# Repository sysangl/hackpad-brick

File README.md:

> This was a hackpad built for Hackclub's YSWS. Check them out [here](https://hackclub.com/)!

## Overview
I'm lazy, so what better thing to do than spend hours learning how to and trying to design a PCB and case for a macro pad, just so I can save milliseconds pressing one key instead of two.s

After days of wondering which way diodes should face in a keyboard matrix, I present the macroPAD (such original naming, i know).

## TODO
- I will finish/refine the KMK code when I have the PCB
- Design an angled stand.
- Rotary Encoder Knob.

## Features
- Outfitted with enough keys to play games such as Minecraft
- Quick-switch keybind profiles, in case you're like me and keep switching between something productive and something not
- Nice little OLED screen for all the customisation you would never need
- And, an integrated stand built into the case (if I remembered to add it)

## SCHEMATIC
![[PCB Schematic]](./assets/SCHEM.png)

## PCB
![[PCB]](./assets/PCB.png)

## CASE
The case went through 4 major redesigns, and will probably change again in the future.
![[Case Design in Fusion]](./assets/CaseV3.png)
![[Case Design in Fusion]](./assets/CaseV3-Main.png)

## BOM:
What you need:
- 11x Cherry MX Switches
- 11x DSA Keycaps
- 5x M3x5x4 Heatset inserts
- 4x M3x16mm SHCS Bolts
- 1x M3x12mm SHCS Bolts
- 12x 1N4148 DO-35 Diodes.
- 1x 0.91" 128x32 OLED Display
- 1x EC11 Rotary Encoder
- 1x XIAO RP2040
- 1x 3D Printed Case (Top Cover & Main Case - Black, Middle Plate - White)

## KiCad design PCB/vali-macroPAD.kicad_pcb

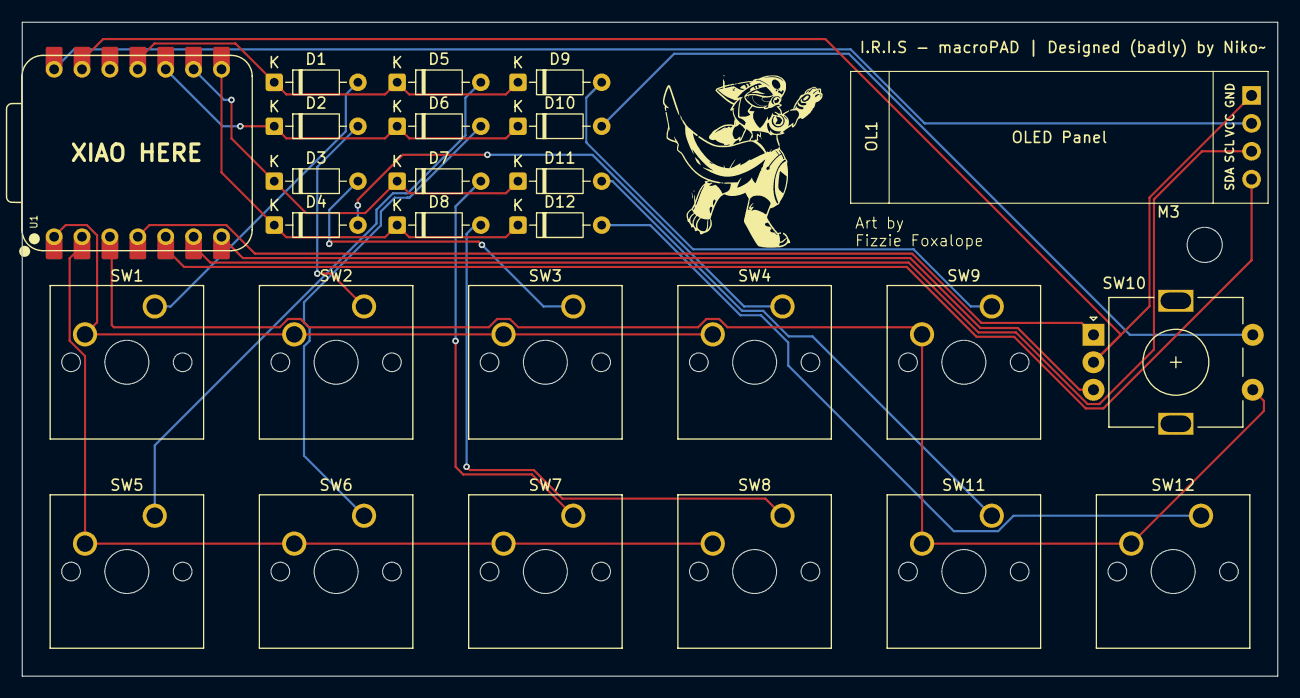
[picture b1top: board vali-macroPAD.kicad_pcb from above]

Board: 2 copper layers, 114.3 x 59.5 mm, 27 parts (0 on the bottom side), 25 nets.

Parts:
D1, D2, D3, D4, D5, D6, D7, D8, D9, D10, D11, D12: 1N4148; D_DO-35_SOD27_P7.62mm_Horizontal
M3: MountingHole_3.2mm_M3
OL1: OLED; SSD1306-0.91-OLED-4pin-128x32
SW1, SW2, SW3, SW4, SW5, SW6, SW7, SW8, SW9, SW11, SW12: SW_Push; SW_Cherry_MX_1.00u_PCB
SW10: RotaryEncoder_Switch; RotaryEncoder_Alps_EC11E-Switch_Vertical_H20mm
U1: XIAO-RP2040-DIP

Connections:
Col1: D1.1 (K), D5.1 (K), D9.1 (K), U1.11 (GPIO3/MOSI)
Col2: D2.1 (K), D6.1 (K), D10.1 (K), U1.10 (GPIO4/MISO)
Col3: D3.1 (K), D7.1 (K), D11.1 (K), U1.9 (GPIO2/SCK)
Col4: D4.1 (K), D8.1 (K), D12.1 (K), U1.8 (GPIO1/RX)
GND: OL1.1 (SDA), SW10.C, U1.13 (GND)
unnamed: D1.2 (A), SW1.1
unnamed: D2.2 (A), SW2.1
unnamed: D3.2 (A), SW3.1
unnamed: D4.2 (A), SW4.1
unnamed: D5.2 (A), SW5.1
unnamed: D6.2 (A), SW6.1
unnamed: D7.2 (A), SW7.1
unnamed: D8.2 (A), SW8.1
unnamed: D9.2 (A), SW9.1
unnamed: D10.2 (A), SW10.S2
unnamed: D11.2 (A), SW11.1
unnamed: D12.2 (A), SW12.1
OLEDSCL: OL1.3 (VCC), U1.6 (GPIO7/SCL)
OLEDSDA: OL1.4 (GND), U1.5 (GPIO6/SDA)
REA: SW10.A, U1.4 (GPIO29/ADC3/A3)
REB: SW10.B, U1.7 (GPIO0/TX)
Row1: SW1.2, SW2.2, SW3.2, SW4.2, U1.1 (GPIO26/ADC0/A0)
Row2: SW5.2, SW6.2, SW7.2, SW8.2, U1.2 (GPIO27/ADC1/A1)
Row3: SW9.2, SW10.S1, SW11.2, SW12.2, U1.3 (GPIO28/ADC2/A2)
VCC: OL1.2 (SCL), U1.14 (VBUS)

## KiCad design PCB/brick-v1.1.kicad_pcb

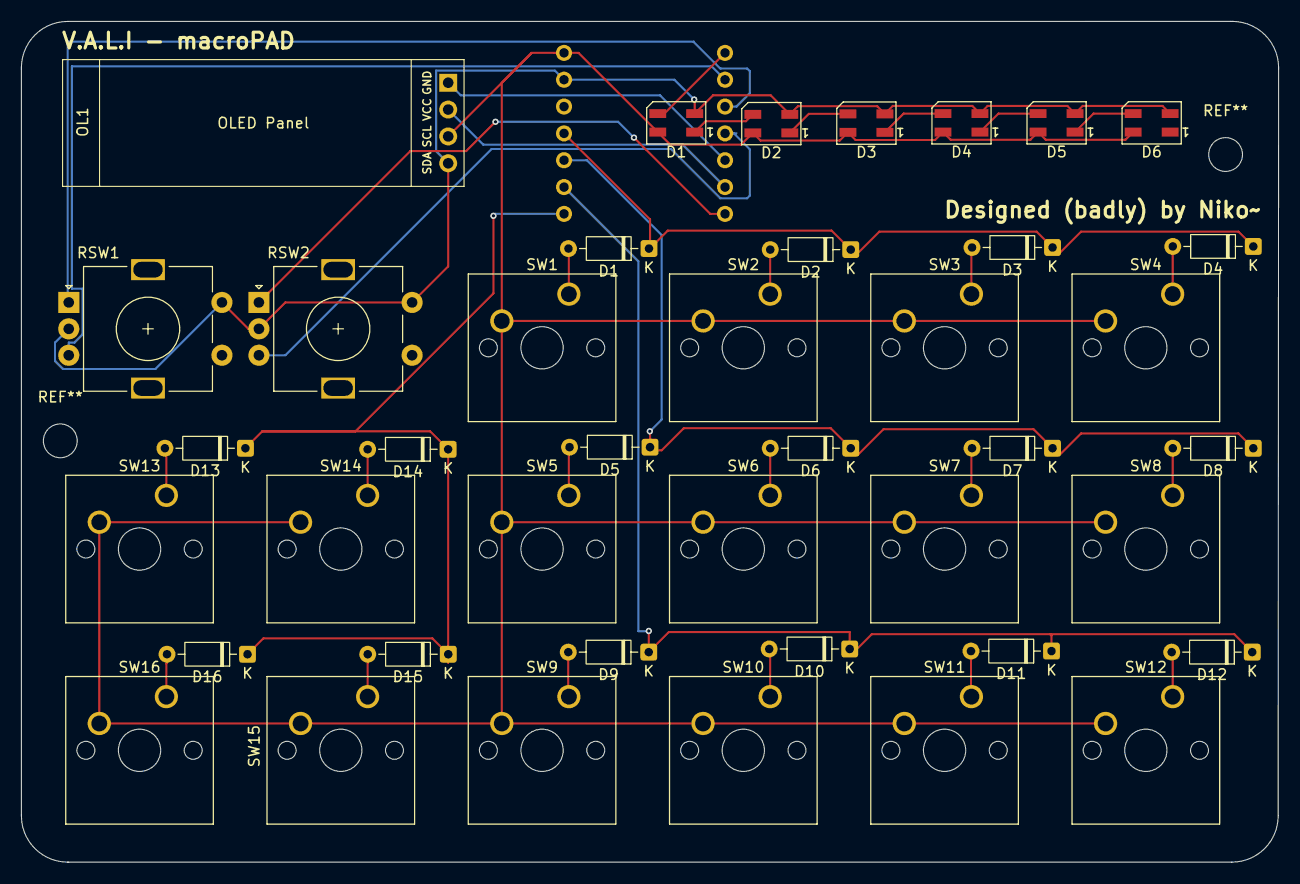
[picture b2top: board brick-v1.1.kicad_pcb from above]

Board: 2 copper layers, 119.0 x 79.6 mm, 42 parts (1 on the bottom side), 34 nets.

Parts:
D1, D2#2, D3#2, D4, D5#2, D6#2, D7, D8, D9, D10, D11, D12, D13, D14, D15, D16: 1N4148; D_DO-35_SOD27_P7.62mm_Horizontal
D1#2, D2, D3, D4#2, D5, D6: SK6812MINI; LED_SK6812MINI_PLCC4_3.5x3.5mm_P1.75mm
OL1: OLED; SSD1306-0.91-OLED-4pin-128x32
RSW1, RSW2: RotaryEncoder_Switch; RotaryEncoder_Alps_EC11E-Switch_Vertical_H20mm
SW1, SW2, SW3, SW4, SW5, SW6, SW7, SW8, SW9, SW10, SW11, SW12, SW13, SW14, SW15, SW16: SW_Push; SW_Cherry_MX_1.00u_PCB
U1: XIAO-RP2040-DIP

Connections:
+5V: D1#2.4 (VDD), D2.4 (VDD), D3.4 (VDD), D4#2.4 (VDD), D5.4 (VDD), D6.4 (VDD), OL1.3 (VCC), SW1.2, SW2.2, SW3.2, SW4.2, SW5.2, SW6.2, SW7.2, SW8.2, SW9.2, SW10.2, SW11.2, SW12.2, SW13.2, SW14.2, SW15.2, SW16.2, U1.14 (VBUS)
GND: D1#2.2 (VSS), D2.2 (VSS), D3.2 (VSS), D4#2.2 (VSS), D5.2 (VSS), D6.2 (VSS), OL1.4 (GND), RSW1.C, RSW1.S2, RSW2.C, RSW2.S2, U1.13 (GND)
unnamed: D1#2.3 (DIN), U1.1 (GPIO26/ADC0/A0)
unnamed: D1#2.1 (DOUT), D2.3 (DIN)
unnamed: D2.1 (DOUT), D3.3 (DIN)
unnamed: D3.1 (DOUT), D4#2.3 (DIN)
unnamed: D4#2.1 (DOUT), D5.3 (DIN)
unnamed: D5.1 (DOUT), D6.3 (DIN)
unnamed: D1.2 (A), SW1.1
unnamed: D1.1 (K), D2#2.1 (K), D3#2.1 (K), D4.1 (K), U1.11 (GPIO3/MOSI)
unnamed: D2#2.2 (A), SW2.1
unnamed: D3#2.2 (A), SW3.1
unnamed: D4.2 (A), SW4.1
unnamed: D5#2.2 (A), SW5.1
unnamed: D5#2.1 (K), D6#2.1 (K), D7.1 (K), D8.1 (K), U1.10 (GPIO4/MISO)
unnamed: D6#2.2 (A), SW6.1
unnamed: D7.2 (A), SW7.1
unnamed: D8.2 (A), SW8.1
unnamed: D9.2 (A), SW9.1
unnamed: D9.1 (K), D10.1 (K), D11.1 (K), D12.1 (K), U1.9 (GPIO2/SCK)
unnamed: D10.2 (A), SW10.1
unnamed: D11.2 (A), SW11.1
unnamed: D12.2 (A), SW12.1
unnamed: D13.2 (A), SW13.1
unnamed: D13.1 (K), D14.1 (K), D15.1 (K), D16.1 (K), U1.8 (GPIO1/RX)
unnamed: D14.2 (A), SW14.1
unnamed: D16.2 (A), SW16.1
unnamed: D15.2 (A), SW15.1
unnamed: OL1.2 (SCL), U1.6 (GPIO7/SCL)
unnamed: OL1.1 (SDA), U1.5 (GPIO6/SDA)
unnamed: RSW2.A, U1.7 (GPIO0/TX)
unnamed: RSW1.B, U1.2 (GPIO27/ADC1/A1)
unnamed: RSW1.A, U1.3 (GPIO28/ADC2/A2)
unnamed: RSW2.B, U1.4 (GPIO29/ADC3/A3)

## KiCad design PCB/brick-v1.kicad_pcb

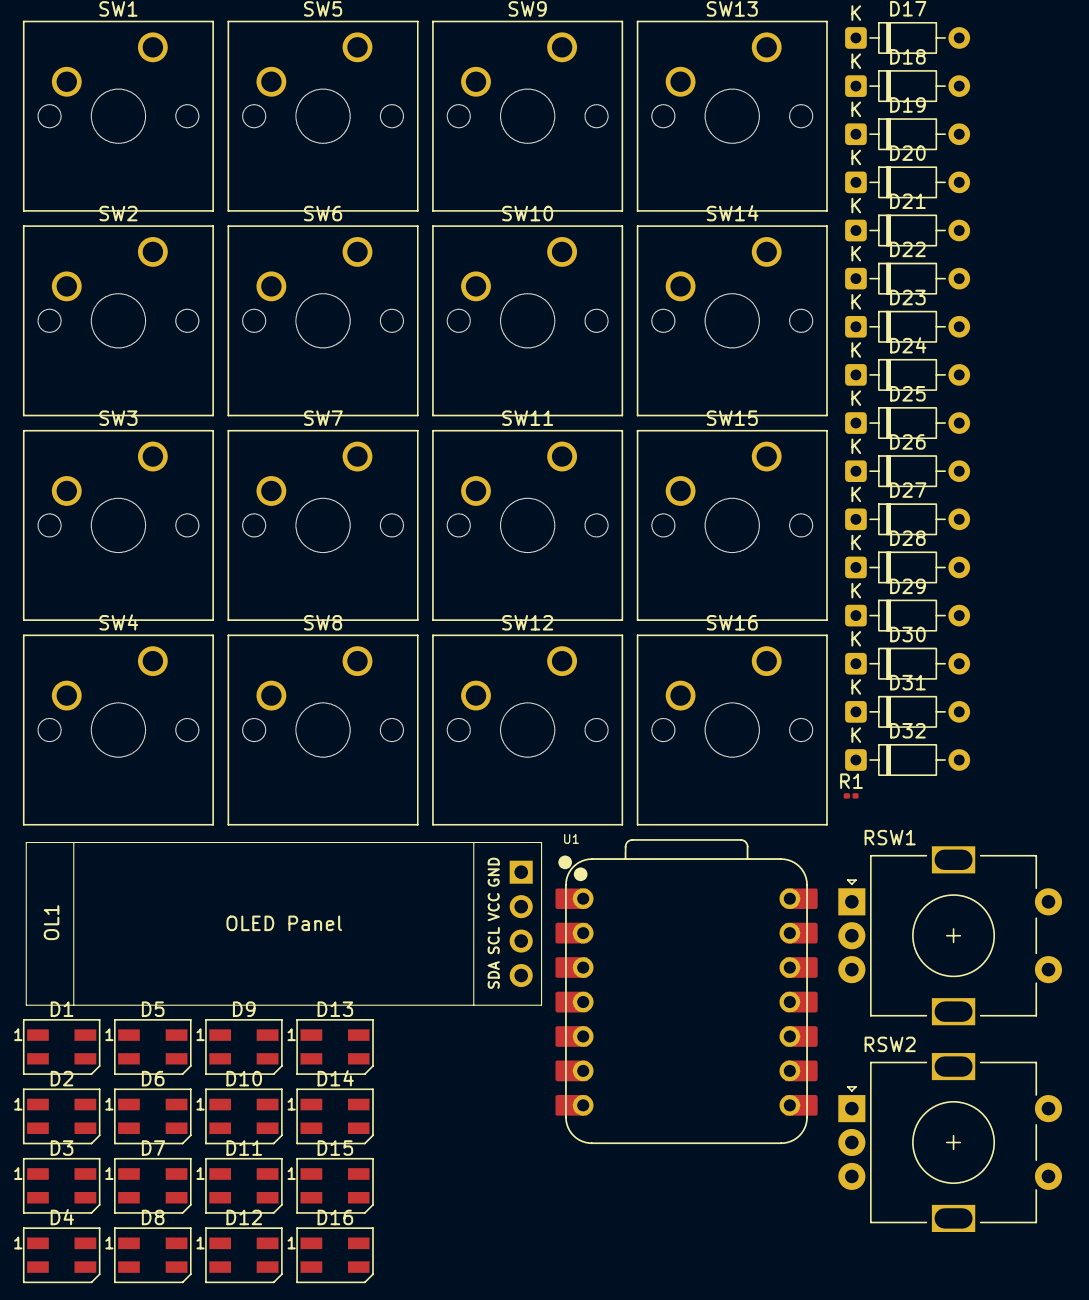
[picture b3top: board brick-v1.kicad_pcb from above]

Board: 2 copper layers, 53 parts (0 on the bottom side), 47 nets, no tracks yet.

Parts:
D1, D2, D3, D4, D5, D6, D7, D8, D9, D10, D11, D12, D13, D14, D15, D16: SK6812MINI; LED_SK6812MINI_PLCC4_3.5x3.5mm_P1.75mm
D17, D18, D19, D20, D21, D22, D23, D24, D25, D26, D27, D28, D29, D30, D31, D32: 1N4148; D_DO-35_SOD27_P7.62mm_Horizontal
OL1: OLED; SSD1306-0.91-OLED-4pin-128x32
R1: R; R_0201_0603Metric
RSW1, RSW2: RotaryEncoder_Switch; RotaryEncoder_Alps_EC11E-Switch_Vertical_H20mm
SW1, SW2, SW3, SW4, SW5, SW6, SW7, SW8, SW9, SW10, SW11, SW12, SW13, SW14, SW15, SW16: SW_Push; SW_Cherry_MX_1.00u_PCB
U1: XIAO-RP2040-DIP

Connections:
+5V: D1.4 (VDD), D2.4 (VDD), D3.4 (VDD), D4.4 (VDD), D5.4 (VDD), D6.4 (VDD), D7.4 (VDD), D8.4 (VDD), D9.4 (VDD), D10.4 (VDD), D11.4 (VDD), D12.4 (VDD), D13.4 (VDD), D14.4 (VDD), D15.4 (VDD), D16.4 (VDD), OL1.3 (VCC), SW1.2, SW2.2, SW3.2, SW4.2, SW5.2, SW6.2, SW7.2, SW8.2, SW9.2, SW10.2, SW11.2, SW12.2, SW13.2, SW14.2, SW15.2, SW16.2, U1.14 (VBUS)
GND: D1.2 (VSS), D2.2 (VSS), D3.2 (VSS), D4.2 (VSS), D5.2 (VSS), D6.2 (VSS), D7.2 (VSS), D8.2 (VSS), D9.2 (VSS), D10.2 (VSS), D11.2 (VSS), D12.2 (VSS), D13.2 (VSS), D14.2 (VSS), D15.2 (VSS), D16.2 (VSS), OL1.4 (GND), U1.13 (GND)
unnamed: D1.3 (DIN), U1.1 (GPIO26/ADC0/A0)
unnamed: D1.1 (DOUT), D2.3 (DIN)
unnamed: D2.1 (DOUT), D3.3 (DIN)
unnamed: D3.1 (DOUT), D4.3 (DIN)
unnamed: D4.1 (DOUT), R1.1
unnamed: D5.1 (DOUT), D6.3 (DIN)
unnamed: D6.1 (DOUT), D7.3 (DIN)
unnamed: D7.1 (DOUT), D8.3 (DIN)
unnamed: D8.1 (DOUT), D9.3 (DIN)
unnamed: D9.1 (DOUT), D10.3 (DIN)
unnamed: D11.3 (DIN), R1.2
unnamed: D11.1 (DOUT), D12.3 (DIN)
unnamed: D12.1 (DOUT), D13.3 (DIN)
unnamed: D13.1 (DOUT), D14.3 (DIN)
unnamed: D14.1 (DOUT), D15.3 (DIN)
unnamed: D15.1 (DOUT), D16.3 (DIN)
unnamed: D5.3 (DIN), D16.1 (DOUT)
unnamed: D17.2 (A), SW1.1
unnamed: D17.1 (K), D18.1 (K), D19.1 (K), D20.1 (K), U1.11 (GPIO3/MOSI)
unnamed: D18.2 (A), SW2.1
unnamed: D19.2 (A), SW3.1
unnamed: D20.2 (A), SW4.1
unnamed: D21.2 (A), SW5.1
unnamed: D21.1 (K), D22.1 (K), D23.1 (K), D24.1 (K), U1.10 (GPIO4/MISO)
unnamed: D22.2 (A), SW6.1
unnamed: D23.2 (A), SW7.1
unnamed: D24.2 (A), SW8.1
unnamed: D25.2 (A), SW9.1
unnamed: D25.1 (K), D26.1 (K), D27.1 (K), D28.1 (K), U1.9 (GPIO2/SCK)
unnamed: D26.2 (A), SW10.1
unnamed: D27.2 (A), SW11.1
unnamed: D28.2 (A), SW12.1
unnamed: D29.2 (A), SW13.1
unnamed: D29.1 (K), D30.1 (K), D31.1 (K), D32.1 (K), U1.8 (GPIO1/RX)
unnamed: D30.2 (A), SW14.1
unnamed: D31.2 (A), SW16.1
unnamed: D32.2 (A), SW15.1
unnamed: OL1.2 (SCL), U1.6 (GPIO7/SCL)
unnamed: OL1.1 (SDA), U1.5 (GPIO6/SDA)
unnamed: RSW1.C, RSW1.S2
unnamed: RSW2.C, RSW2.S2
unnamed: RSW2.A, U1.7 (GPIO0/TX)
unnamed: RSW1.B, U1.2 (GPIO27/ADC1/A1)
unnamed: RSW1.A, U1.3 (GPIO28/ADC2/A2)
unnamed: RSW2.B, U1.4 (GPIO29/ADC3/A3)

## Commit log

2025-12-03 - Created the schematics and PCB board version 1.1 - Started to design the case
2025-12-05 Redesigned the PCB, and reenamed to macroPAD. Design now features a 2x6 layout and 1 rotary encoder
2025-12-05 Tidied up wire routes
2025-12-06 reogranised folders
2025-12-06 Designed the case Started to code the firmware using KMK
2025-12-06 Started README
2025-12-06 dhfe5rhf
2025-12-07 Started to write the readdme and got distracteed by minecraft
2025-12-09 Updated firmware, should work on the pad but I cant test it yet.
2025-12-10 Created a better case design.
2025-12-10 Fixed broken image link
2025-12-10 Fixing more broken image links
2025-12-10 Cleaned up README
2025-12-10 bybsdghj5ee5
2025-12-16 Forgot to upload the updated case, also included thee .3mf file
2026-01-01 Changed board pins from GP to D Switcheed to KMK's Display extension instead of peg_oled_display
2026-01-01 Actually comitting the changes for the previous commit... oops
2026-01-01 Forgot to upload and update CAD files. V2 had no support for the pcb, so using the keys would cause the pcb to bendd slightly. The plate was also located too far down which has now been fixed in V3. 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
    V3 also removes a significant amount from the top cover, opting for just a rim to hold thee heeat-set inserts. It wasn't easy to see the OLED display and I wantedd to show the protogen on the silkscr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
2026-01-01 aSdger
2026-01-01 Brokeen readme
2026-01-01 readme???
2026-01-01 apparently i dont know how MD links work
